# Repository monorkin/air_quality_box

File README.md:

# Air Quality Box

This is a [ESPHome](https://esphome.io/) powered (integrated
with [Home Assistant](https://www.home-assistant.io/))
in-door air quality meter with a display.

It measures:
* **CO₂ concentration**
* **Relative humidity**
* **Temperature**
* **Atmospheric pressure**
* **Air conductivity**
* **Dust particles <1µm weight concentration**
* **Dust particles <2.5µm weight concentration**
* **Dust particles <4µm weight concentration**
* **Dust particles <10µm weight concentration**

## Assembly

This project is split into three parts, each with it's own steps:
1. [Printed circuit board](./pcb/)
2. [Firmware](./firmware/)
3. [3D printed case](./case/)

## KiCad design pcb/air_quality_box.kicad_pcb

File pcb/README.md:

# PCB

The PCB connects all components into a single device.
It routes power and signals from the micro-controller to each sensor, and it
does some basic power filtering.

## Development

The PCB is developed using [KiCad v5](https://www.kicad.org/download/).
All symbols, footprints and models can only be from the standard library or
contained within this project.

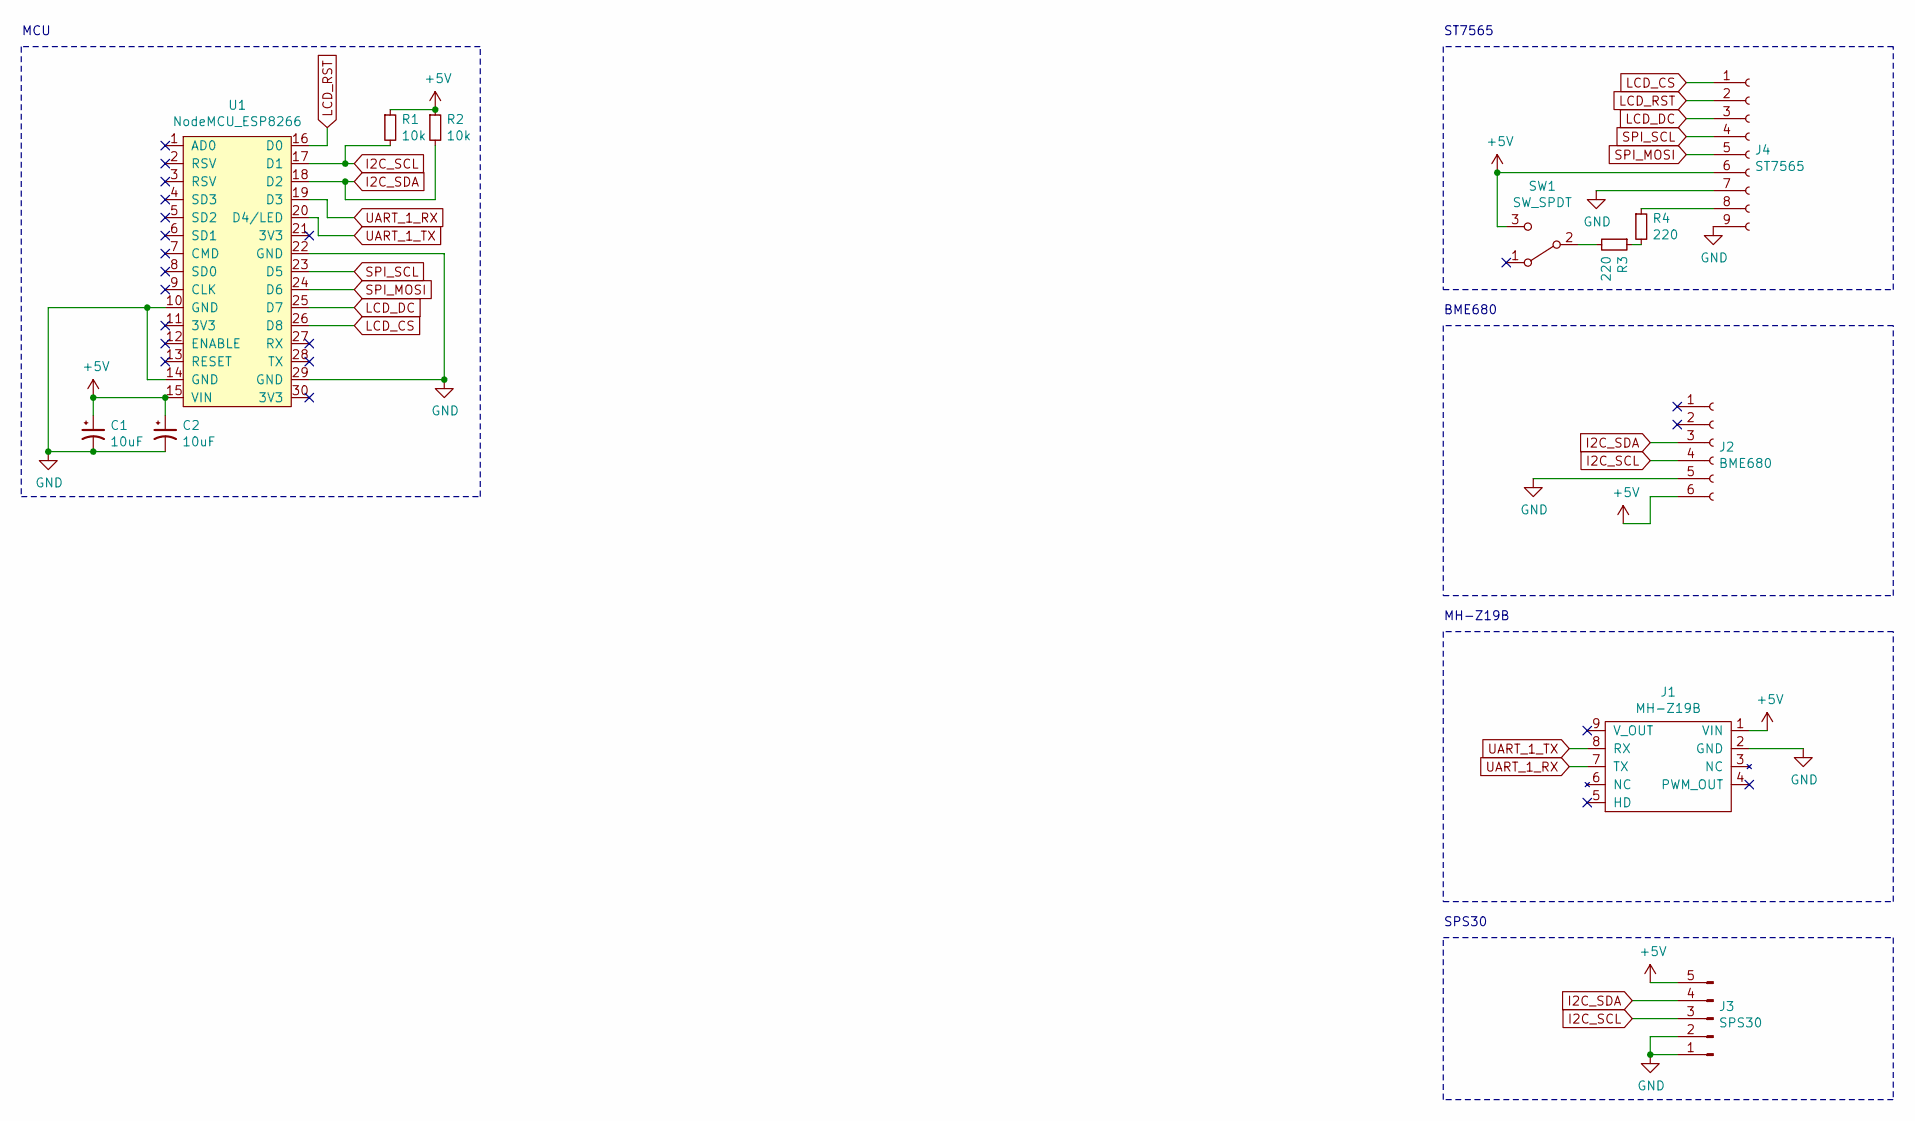
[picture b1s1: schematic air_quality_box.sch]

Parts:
C1, C2: 10uF; CP_Radial_D5.0mm_P2.50mm
J1: MH-Z19B
J2: BME680; PinHeader_1x06_P2.54mm_Vertical
J3: SPS30; ZH_1.5mm_5P
J4: ST7565; PinHeader_1x09_P2.54mm_Vertical
R1, R2: 10k; R_Axial_DIN0207_L6.3mm_D2.5mm_P10.16mm_Horizontal
R3, R4: 220; R_Axial_DIN0207_L6.3mm_D2.5mm_P10.16mm_Horizontal
SW1: SW_SPDT; switch
U1: NodeMCU_ESP8266

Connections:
+5V: C1.1, C2.1, J1.1 (VIN), J2.6, J3.5, J4.6, R1.1, R2.1, SW1.3 (C), U1.15 (VIN)
GND: C1.2, C2.2, J1.2 (GND), J2.5, J3.1, J3.2, J4.7, J4.9, U1.10 (GND), U1.14 (GND), U1.22 (GND), U1.29 (GND)
I2C_SCL: J2.4, J3.3, R1.2, U1.17 (D1)
I2C_SDA: J2.3, J3.4, R2.2, U1.18 (D2)
LCD_CS: J4.1, U1.26 (D8)
LCD_DC: J4.3, U1.25 (D7)
LCD_RST: J4.2, U1.16 (D0)
unnamed: J4.8, R4.1
unnamed: R3.1, R4.2
unnamed: R3.2, SW1.2 (B)
SPI_MOSI: J4.5, U1.24 (D6)
SPI_SCL: J4.4, U1.23 (D5)
UART_1_RX: J1.7 (TX), U1.19 (D3)
UART_1_TX: J1.8 (RX), U1.20 (D4/LED)

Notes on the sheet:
ST7565
BME680
MH-Z19B
SPS30
MCU

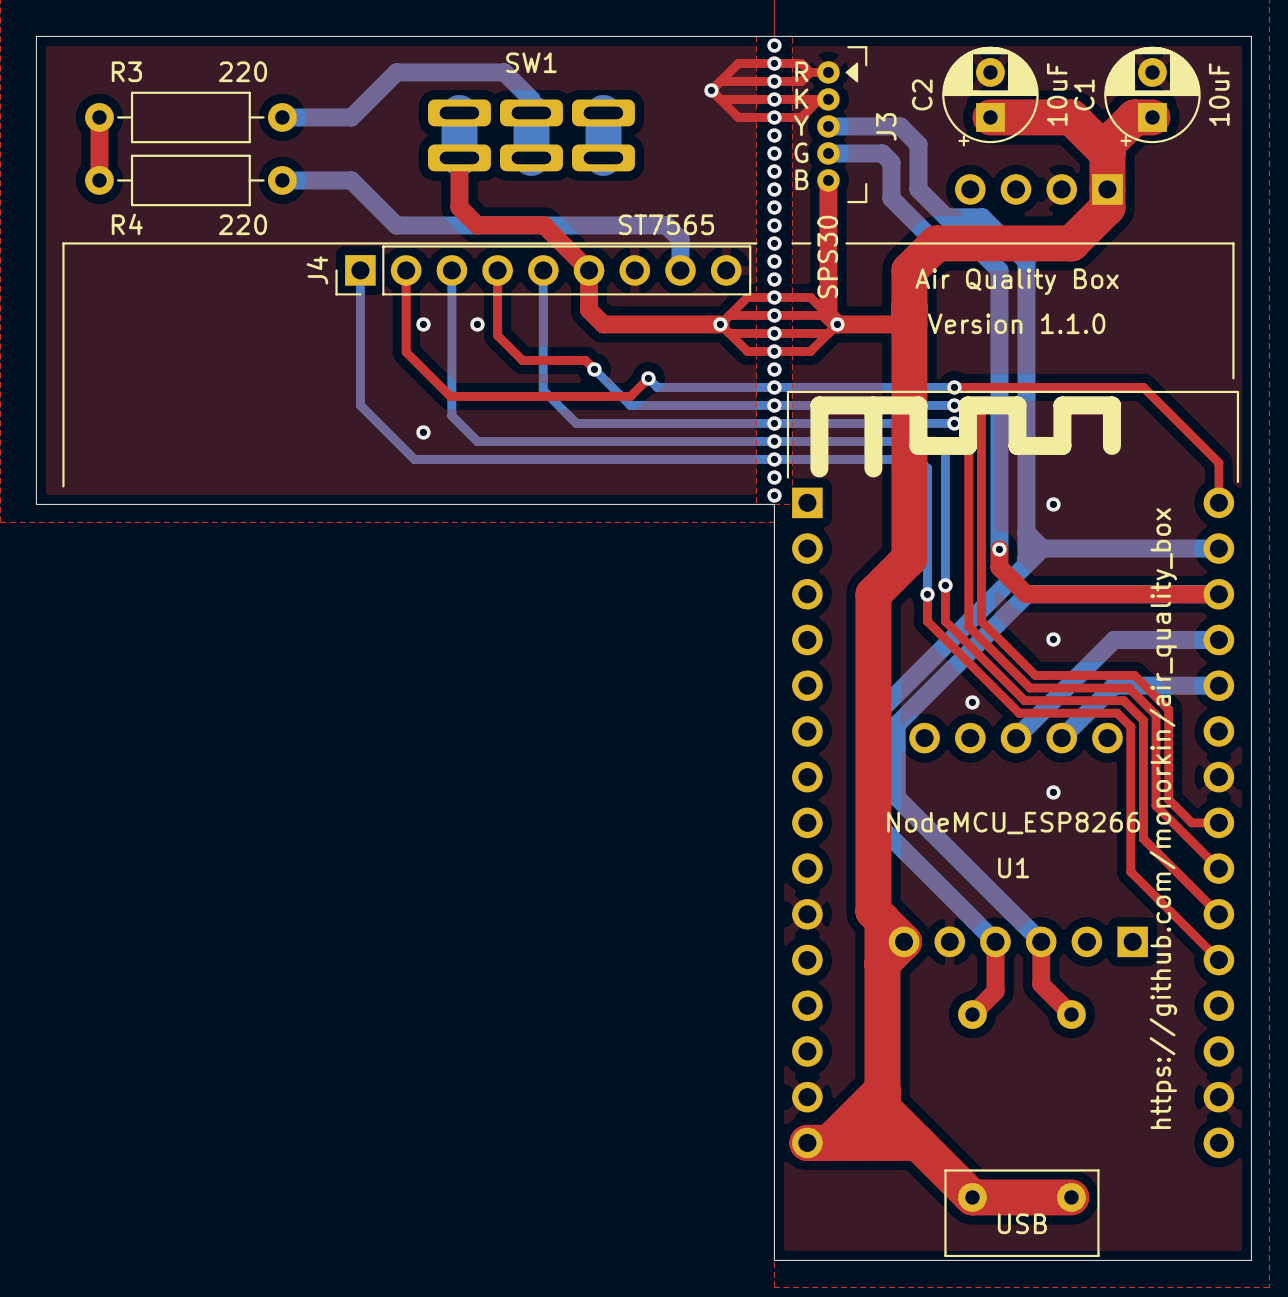
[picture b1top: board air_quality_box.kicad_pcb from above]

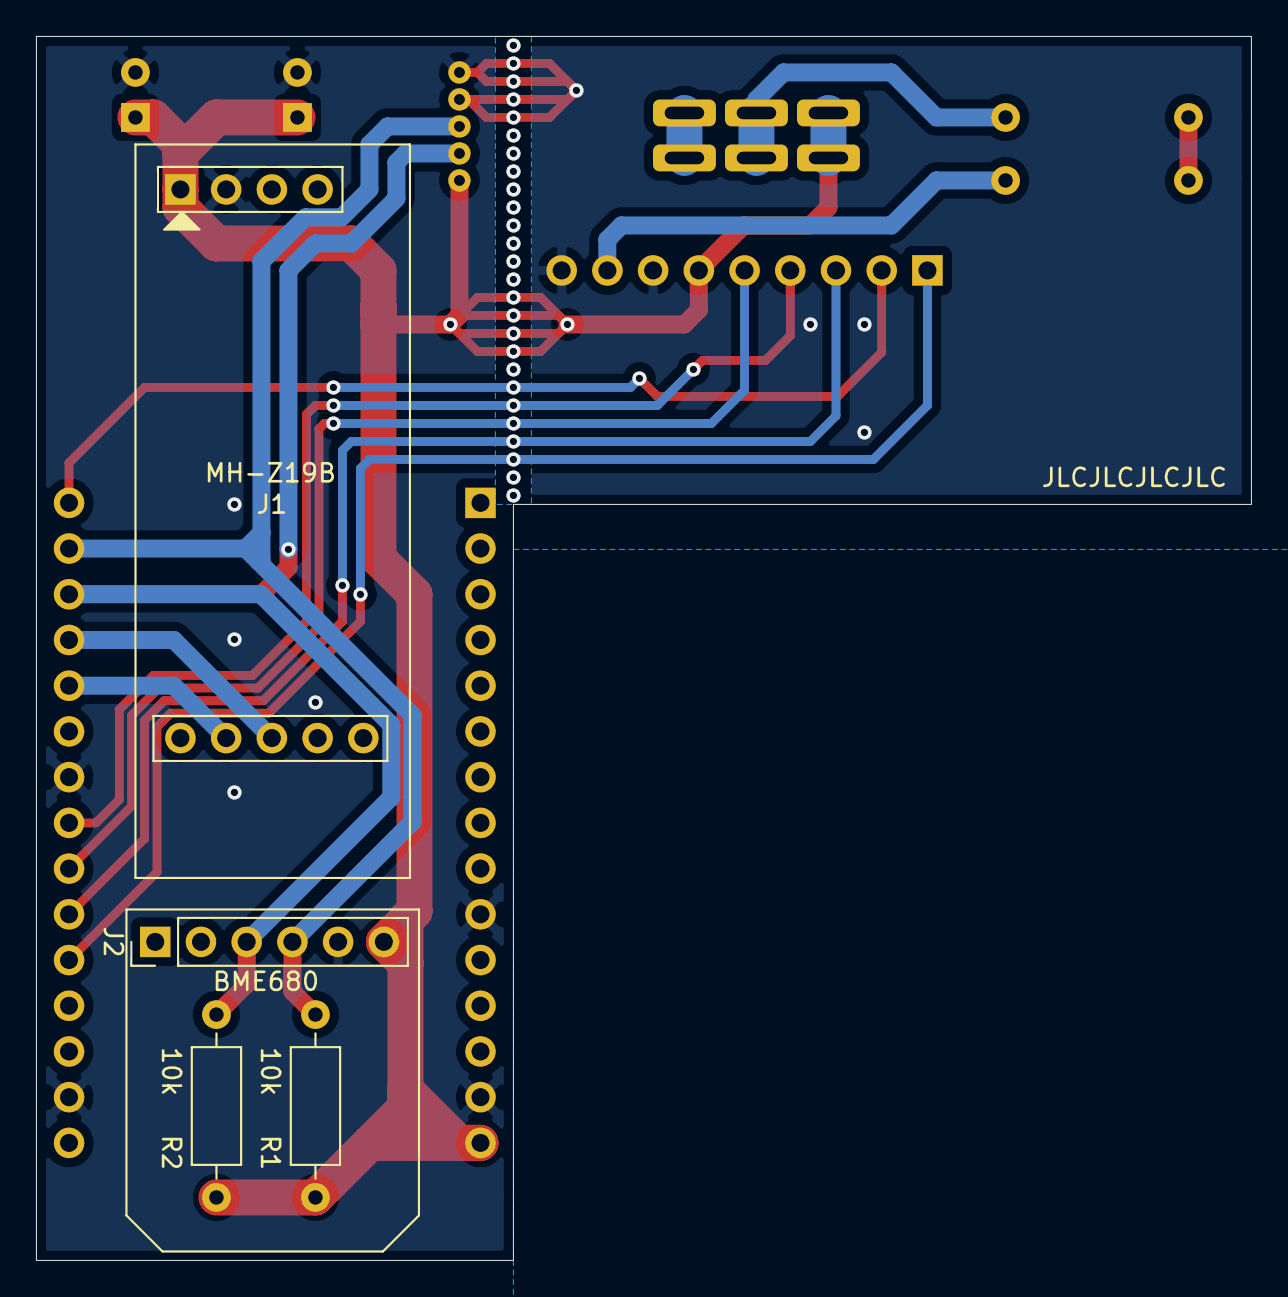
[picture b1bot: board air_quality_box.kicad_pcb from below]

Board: 2 copper layers, 67.5 x 68.0 mm, 12 parts (4 on the bottom side), 14 nets.

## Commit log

2021-10-22 Initial configuration
2021-10-22 Configure display
2021-10-22 License the project under the MIT license
2021-10-22 Create readme file
2021-10-22 Show measurment graphs
2021-10-22 Add graphs to all pages
2021-10-22 Move firmware to separate dir
2021-10-24 Switch I2C lines
    The Node modules have dedicated I2C hardware on pins D1 (SCL) and D2
    (SDA). To avoide possbile conflicts and improve interoperability with
    3rd party libraries the configuration was updated to use these lines
    as well.
2021-10-25 Add basic instructions
2021-10-25 Create sample secrets file
2021-10-25 Explain low particle or CO2 reading issues
2021-10-25 Improve phrasing
2021-10-25 Remove duplicate word
2021-10-25 Rephrase settle-in warning
2021-10-27 Create board schematic
2021-10-27 Add basic purpose explanation to each readme
2021-10-27 Create footprints
2021-10-28 Create basic board layout
2021-10-29 Position the LCD in the center of the board
2021-10-29 Add JCL order number location to board
2021-10-29 Export Gerber and drill files
2021-11-06 Swap VCC and GNC pins on BME680
    This mistake nearly cost me the sensor. To my luck only the regulator
    released the magick smoke. After replacing the regulator the sensor
    started working again.
    Also, the screen diode draws a lot of current. Through experimentation I
    figured out that it's bright enough with just 15mA of current. So I
    added a 440 Ohm load in series with the backlight to limit the current
2021-11-06 Swap DC and CS pins as they are swapped on the PCB
2021-11-06 Change route so that power lanes do not cross
2021-11-08 Basic front face layout
